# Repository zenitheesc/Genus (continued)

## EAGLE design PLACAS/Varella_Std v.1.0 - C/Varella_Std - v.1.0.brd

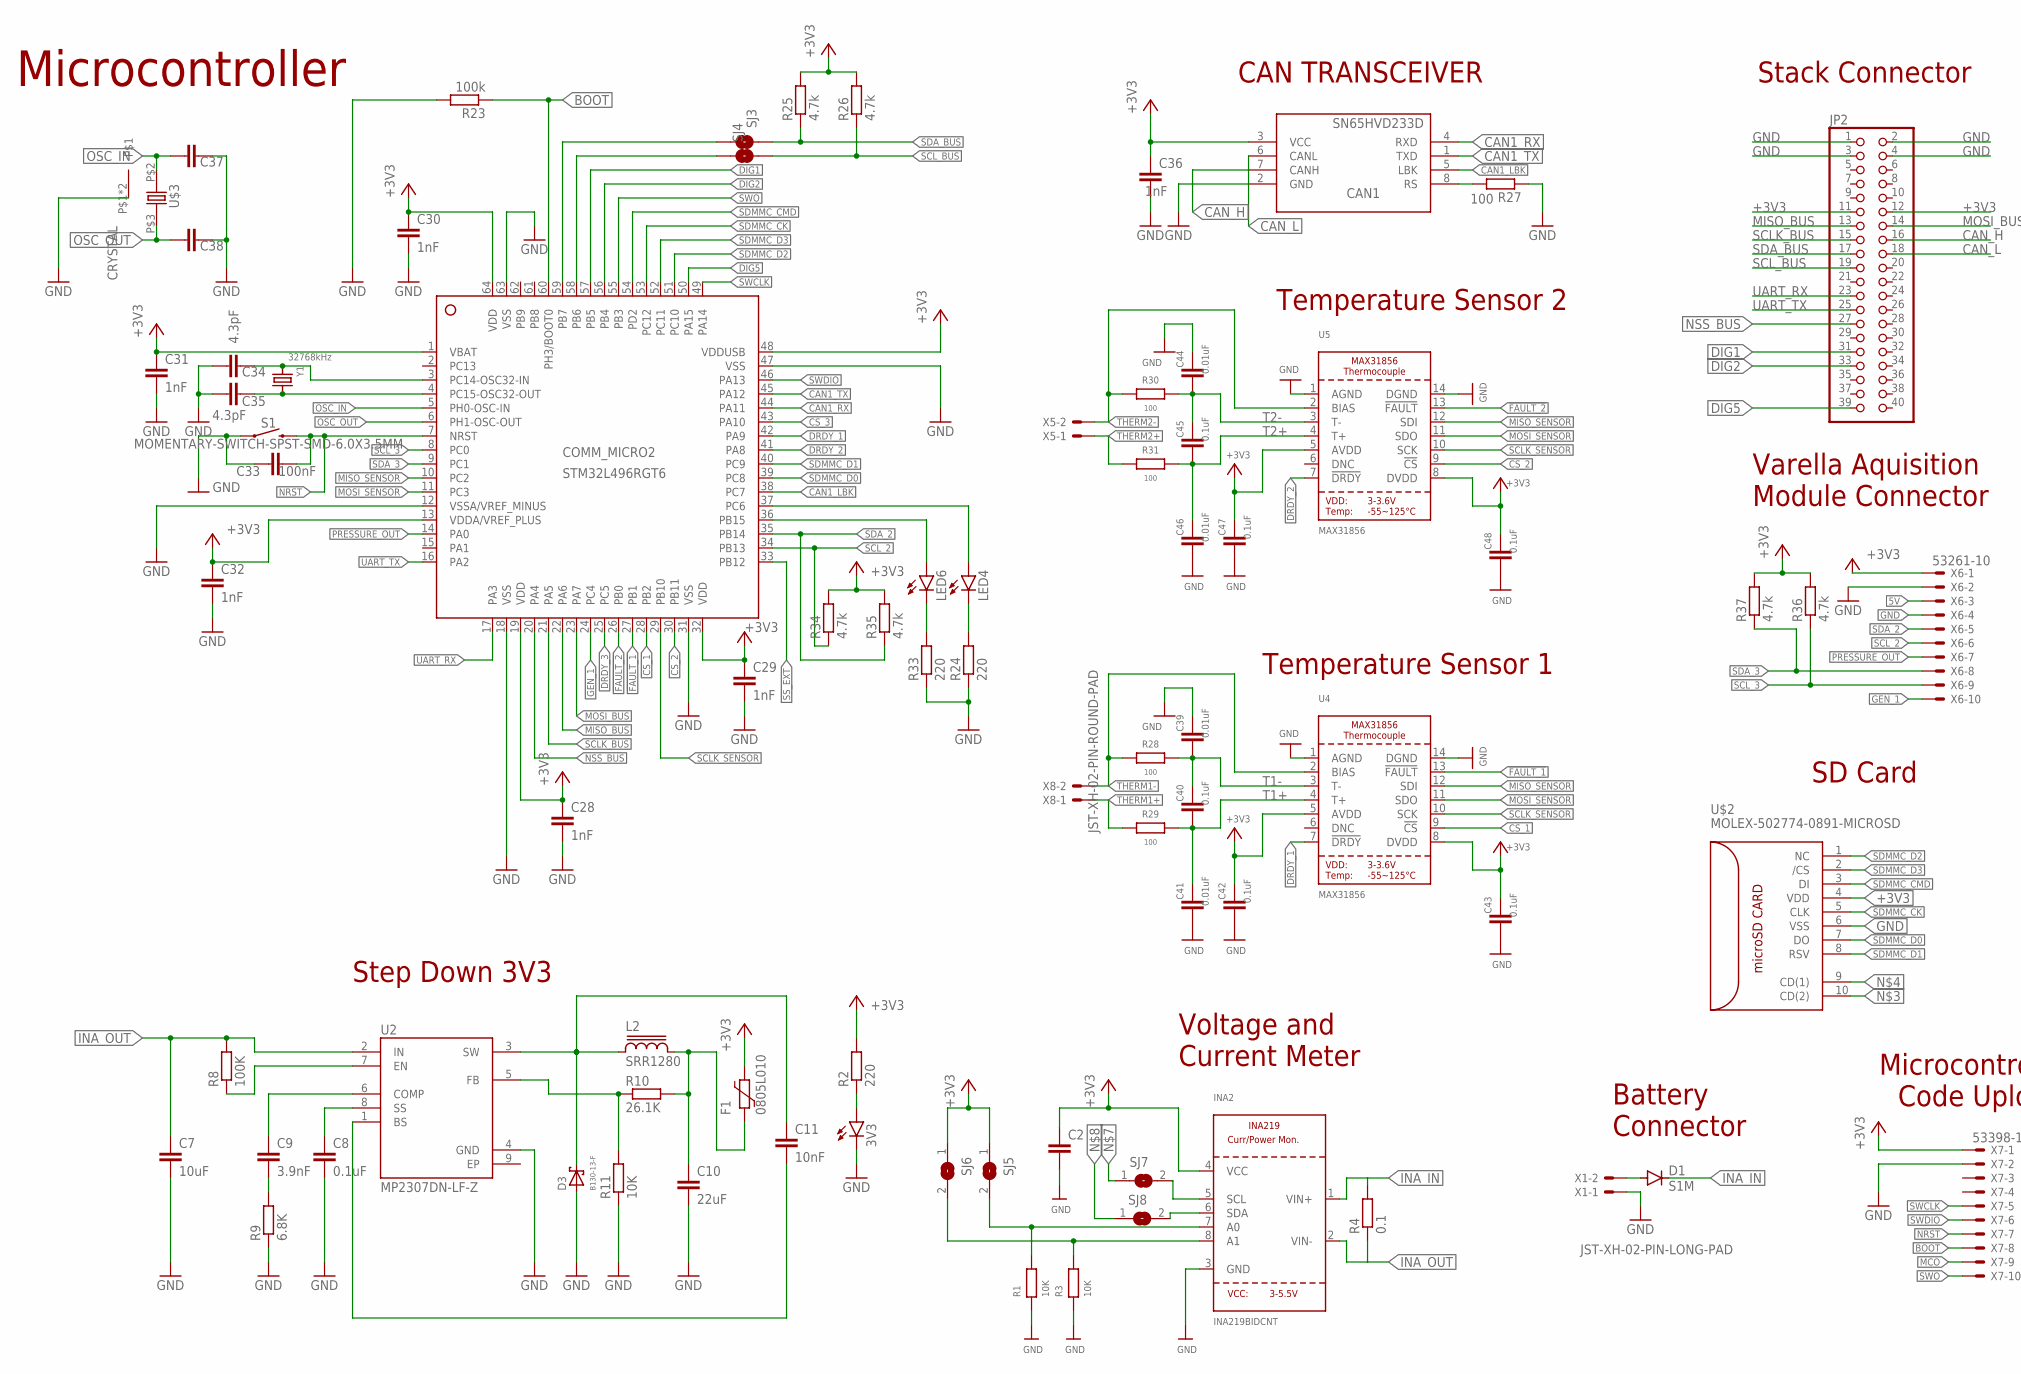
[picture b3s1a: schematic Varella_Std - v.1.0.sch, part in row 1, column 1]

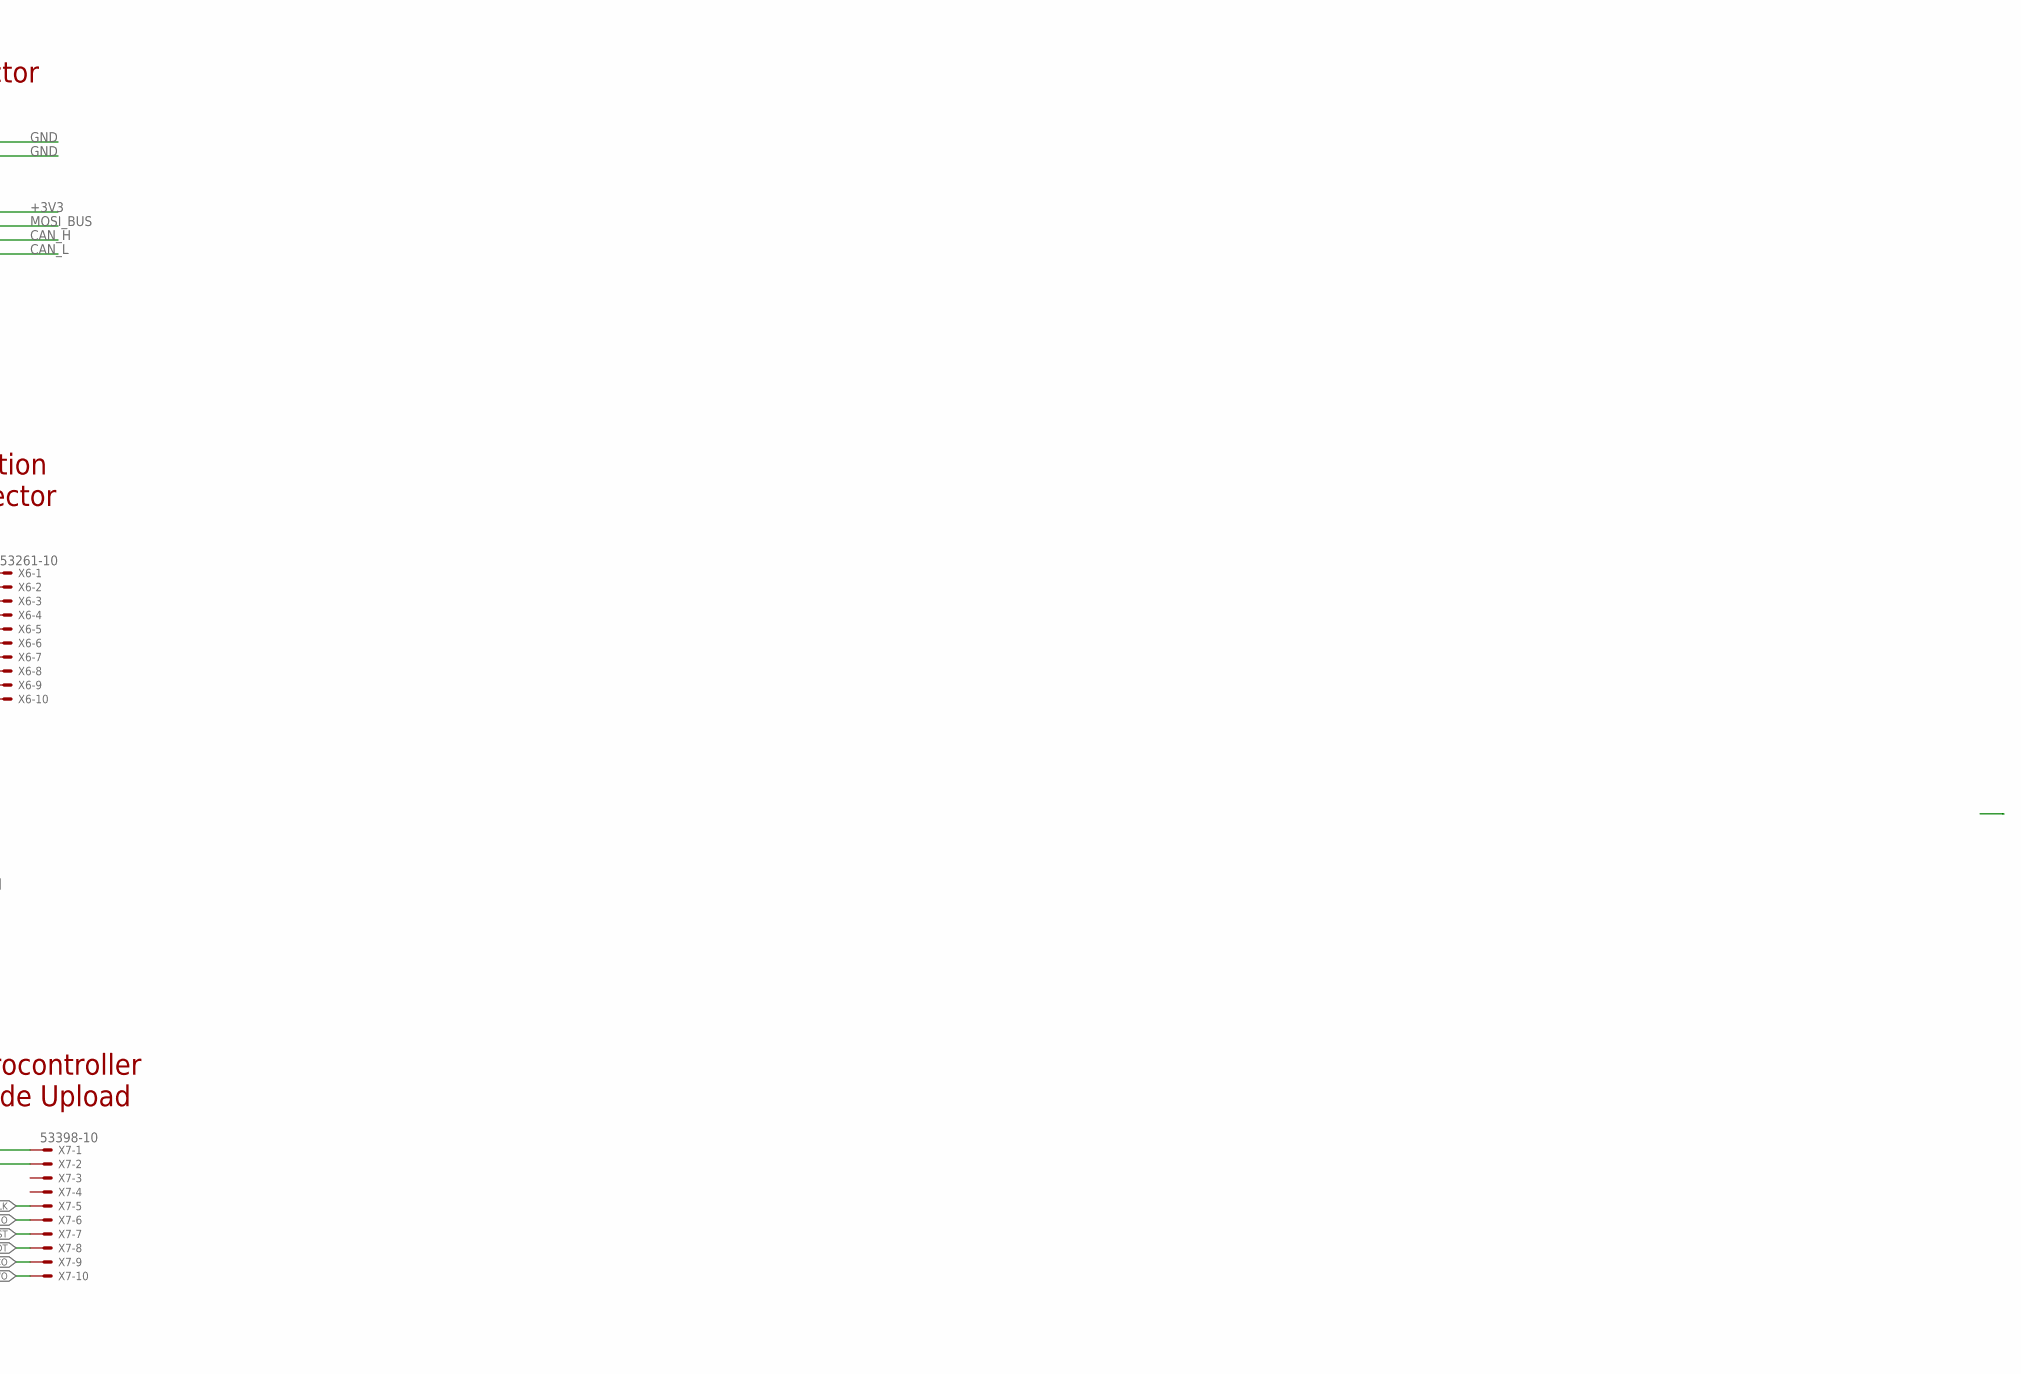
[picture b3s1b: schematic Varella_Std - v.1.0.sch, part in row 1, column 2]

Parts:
3V3: LEDCHIP-LED0805; CHIP-LED0805
C2, C37, C38: C-EUC0805; C0805
C7: 10uF; C0805
C8, C40, C42, C43, C45, C47, C48: 0.1uF; C0805
C9: 3.9nF; C0805
C10: 22uF; C0805
C11: 10nF; C0805
C28, C29, C30, C31, C32, C36: 1nF; C0805
C33: 100nF; C0805
C34, C35: 4.3pF; C0805
C39, C41, C44, C46: 0.01uF; C0805
CAN1: SN65HVD233D; SOIC8
COMM_MICRO2: STM32L496RGT6; LQFP64_10X10
D1: S1M; SMA
D3: B130-13-F; SMA
F1: 0805L010; 0805L
INA2: INA219BIDCNT; SOT23-8
JP2: PINHD-2X20; 2X20
L2: SRR1280
LED4, LED6: LEDCHIP-LED0805; CHIP-LED0805
R1, R3, R11: 10K; R0805
R2, R24, R33: 220; R0805
R4: 0.1; R2512
R8: 100K; R0805
R9: 6.8K; R0805
R10: 26.1K; R0805
R23: 100k; R0805
R25, R26, R34, R35, R36, R37: 4.7k; R0805
R27, R28, R29, R30, R31: 100; R0805
S1: MOMENTARY-SWITCH-SPST-SMD-6.0X3.5MM; TACTILE_SWITCH_SMD_6.0X3.5MM
SJ3, SJ4: SMD-JUMPER-2
SJ5, SJ6, SJ7, SJ8: SOLDERJUMPERREFLOW_NOPASTE; SOLDERJUMPER_REFLOW_NOPASTE
U2: MP2307DN-LF-Z; SOIC127P600X170-9N
U4, U5: MAX31856; TSSOP14
U$2: MOLEX-502774-0891-MICROSD
U$3: CRYSTAL; CRYSTAL_SMD
X1: JST-XH-02-PIN-LONG-PAD; JST-XH-02-PACKAGE-LONG-PAD
X5, X8: JST-XH-02-PIN-ROUND-PAD; JST-XH-02-PACKAGE-ROUND-PAD
X6: 53261-10
X7: 53398-10
Y1: 32768kHz; CRYSTAL_8X3.8

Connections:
5V: X6.3
!FAULT_1: COMM_MICRO2.27 (PB1), U4.13 (!FAULT)
!FAULT_2: COMM_MICRO2.26 (PB0), U5.13 (!FAULT)
+3V3: C2.1, C28.1, C29.1, C30.1, C31.1, C32.1, C36.1, C42.1, C43.1, C47.1, C48.1, CAN1.3 (VCC), COMM_MICRO2.1 (VBAT), COMM_MICRO2.13 (VDDA/VREF_PLUS), COMM_MICRO2.19 (VDD), COMM_MICRO2.32 (VDD), COMM_MICRO2.48 (VDDUSB), COMM_MICRO2.64 (VDD), F1.1, INA2.4 (VCC), JP2.11, JP2.12, R2.2, R25.2, R26.2, R34.2, R35.2, R36.2, R37.2, SJ5.1, SJ6.1, U4.5 (AVDD), U4.8 (DVDD), U5.5 (AVDD), U5.8 (DVDD), U$2.4 (VDD), X6.1, X7.1
BOOT: COMM_MICRO2.60 (PH3/BOOT0), R23.1, X7.8
CAN1_LBK: CAN1.5 (LBK), COMM_MICRO2.38 (PC7)
CAN1_RX: CAN1.4 (RXD), COMM_MICRO2.44 (PA11)
CAN1_TX: CAN1.1 (TXD), COMM_MICRO2.45 (PA12)
CAN_H: CAN1.7 (CANH), JP2.16
CAN_L: CAN1.6 (CANL), JP2.18
CS_1: COMM_MICRO2.28 (PB2), U4.9 (!CS)
CS_2: COMM_MICRO2.30 (PB11), U5.9 (!CS)
CS_3: COMM_MICRO2.43 (PA10)
DIG1: COMM_MICRO2.57 (PB5), JP2.31
DIG2: COMM_MICRO2.56 (PB4), JP2.33
DIG5: COMM_MICRO2.50 (PA15), JP2.39
DRDY_1: COMM_MICRO2.42 (PA9), U4.7 (!DRDY)
DRDY_2: COMM_MICRO2.41 (PA8), U5.7 (!DRDY)
DRDY_3: COMM_MICRO2.25 (PC5)
EP: U2.9 (EP)
GEN_1: COMM_MICRO2.24 (PC4), X6.10
GND: 3V3.C, C2.2, C7.2, C8.2, C10.2, C28.2, C29.2, C30.2, C31.2, C32.2, C33.1, C34.1, C35.1, C36.2, C37.2, C38.2, C39.1, C41.2, C42.2, C43.2, C44.1, C46.2, C47.2, C48.2, CAN1.2 (GND), COMM_MICRO2.12 (VSSA/VREF_MINUS), COMM_MICRO2.18 (VSS), COMM_MICRO2.31 (VSS), COMM_MICRO2.47 (VSS), COMM_MICRO2.63 (VSS), D3.A, INA2.3 (GND), JP2.1, JP2.2, JP2.3, JP2.4, R1.1, R3.1, R9.1, R11.1, R23.2, R24.1, R27.1, R33.1, S1.1, U2.4 (GND), U4.1 (AGND), U4.14 (DGND), U5.1 (AGND), U5.14 (DGND), U$2.6 (VSS), U$3.P$1, U$3.P$4, X1.1, X6.2, X6.4, X7.2
INA_IN: D1.C, INA2.1 (VIN+), R4.2
INA_OUT: C7.1, INA2.2 (VIN-), R4.1, R8.2, U2.2 (IN)
MCO: X7.9
MISO_BUS: COMM_MICRO2.22 (PA6), JP2.13
MISO_SENSOR: COMM_MICRO2.10 (PC2), U4.12 (SDI), U5.12 (SDI)
MOSI_BUS: COMM_MICRO2.23 (PA7), JP2.14
MOSI_SENSOR: COMM_MICRO2.11 (PC3), U4.11 (SDO), U5.11 (SDO)
unnamed: D1.A, X1.2
unnamed: 3V3.A, R2.1
unnamed: INA2.8 (A1), R3.2, SJ6.2, SJ7.1
unnamed: INA2.7 (A0), R1.2, SJ5.2, SJ8.1
unnamed: INA2.5 (SCL), SJ7.2
unnamed: INA2.6 (SDA), SJ8.2
unnamed: R8.1, U2.7 (EN)
unnamed: C9.2, R9.2
unnamed: C8.1, U2.8 (SS)
unnamed: C9.1, U2.6 (COMP)
unnamed: C11.1, D3.C, L2.1, U2.3 (SW)
unnamed: R10.1, R11.2, U2.5 (FB)
unnamed: C11.2, U2.1 (BS)
unnamed: COMM_MICRO2.37 (PC6), LED4.A
unnamed: LED4.C, R24.2
unnamed: C34.2, COMM_MICRO2.3 (PC14-OSC32-IN), Y1.P$1 (1)
unnamed: C35.2, COMM_MICRO2.4 (PC15-OSC32-OUT), Y1.P$4 (2)
unnamed: COMM_MICRO2.59 (PB7), SJ3.1
unnamed: COMM_MICRO2.58 (PB6), SJ4.1
unnamed: CAN1.8 (RS), R27.2
unnamed: COMM_MICRO2.36 (PB15), LED6.A
unnamed: LED6.C, R33.2
NRST: C33.2, COMM_MICRO2.7 (NRST), S1.2, X7.7
NSS_BUS: COMM_MICRO2.20 (PA4), JP2.27
OSC_IN: C37.1, COMM_MICRO2.5 (PH0-OSC-IN), U$3.P$2 (1)
OSC_OUT: C38.1, COMM_MICRO2.6 (PH1-OSC-OUT), U$3.P$3 (2)
OUT: C10.1, F1.2, L2.2, R10.2
PRESSURE_OUT: COMM_MICRO2.14 (PA0), X6.7
SCLK_BUS: COMM_MICRO2.21 (PA5), JP2.15
SCLK_SENSOR: COMM_MICRO2.29 (PB10), U4.10 (SCK), U5.10 (SCK)
SCL_2: COMM_MICRO2.34 (PB13), R34.1, X6.6
SCL_3: COMM_MICRO2.8 (PC0), R36.1, X6.9
SCL_BUS: JP2.19, R26.1, SJ4.2
SDA_2: COMM_MICRO2.35 (PB14), R35.1, X6.5
SDA_3: COMM_MICRO2.9 (PC1), R37.1, X6.8
SDA_BUS: JP2.17, R25.1, SJ3.2
SDMMC_CK: COMM_MICRO2.53 (PC12), U$2.5 (CLK)
SDMMC_CMD: COMM_MICRO2.54 (PD2), U$2.3 (DI)
SDMMC_D0: COMM_MICRO2.39 (PC8), U$2.7 (DO)
SDMMC_D1: COMM_MICRO2.40 (PC9), U$2.8 (RSV)
SDMMC_D2: COMM_MICRO2.51 (PC10), U$2.1 (NC)
SDMMC_D3: COMM_MICRO2.52 (PC11), U$2.2 (/CS)
SS_EXT: COMM_MICRO2.33 (PB12)
SWCLK: COMM_MICRO2.49 (PA14), X7.5
SWDIO: COMM_MICRO2.46 (PA13), X7.6
SWO: COMM_MICRO2.55 (PB3), X7.10
T1+: C40.2, C41.1, R29.2, U4.4 (T+)
T1-: C39.2, C40.1, R28.2, U4.3 (T-)
T2+: C45.2, C46.1, R31.2, U5.4 (T+)
T2-: C44.2, C45.1, R30.2, U5.3 (T-)
THERM1+: R29.1, X8.1
THERM1-: R28.1, U4.2 (BIAS), X8.2
THERM2+: R31.1, X5.1
THERM2-: R30.1, U5.2 (BIAS), X5.2
UART_RX: COMM_MICRO2.17 (PA3), JP2.23
UART_TX: COMM_MICRO2.16 (PA2), JP2.25

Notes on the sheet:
Battery Connector
Voltage and Current Meter
Step Down 3V3
Microcontroller Code Upload
Microcontroller
CAN TRANSCEIVER
Varella Aquisition Module Connector
Temperature Sensor 1
Temperature Sensor 2
Stack Connector
SD Card

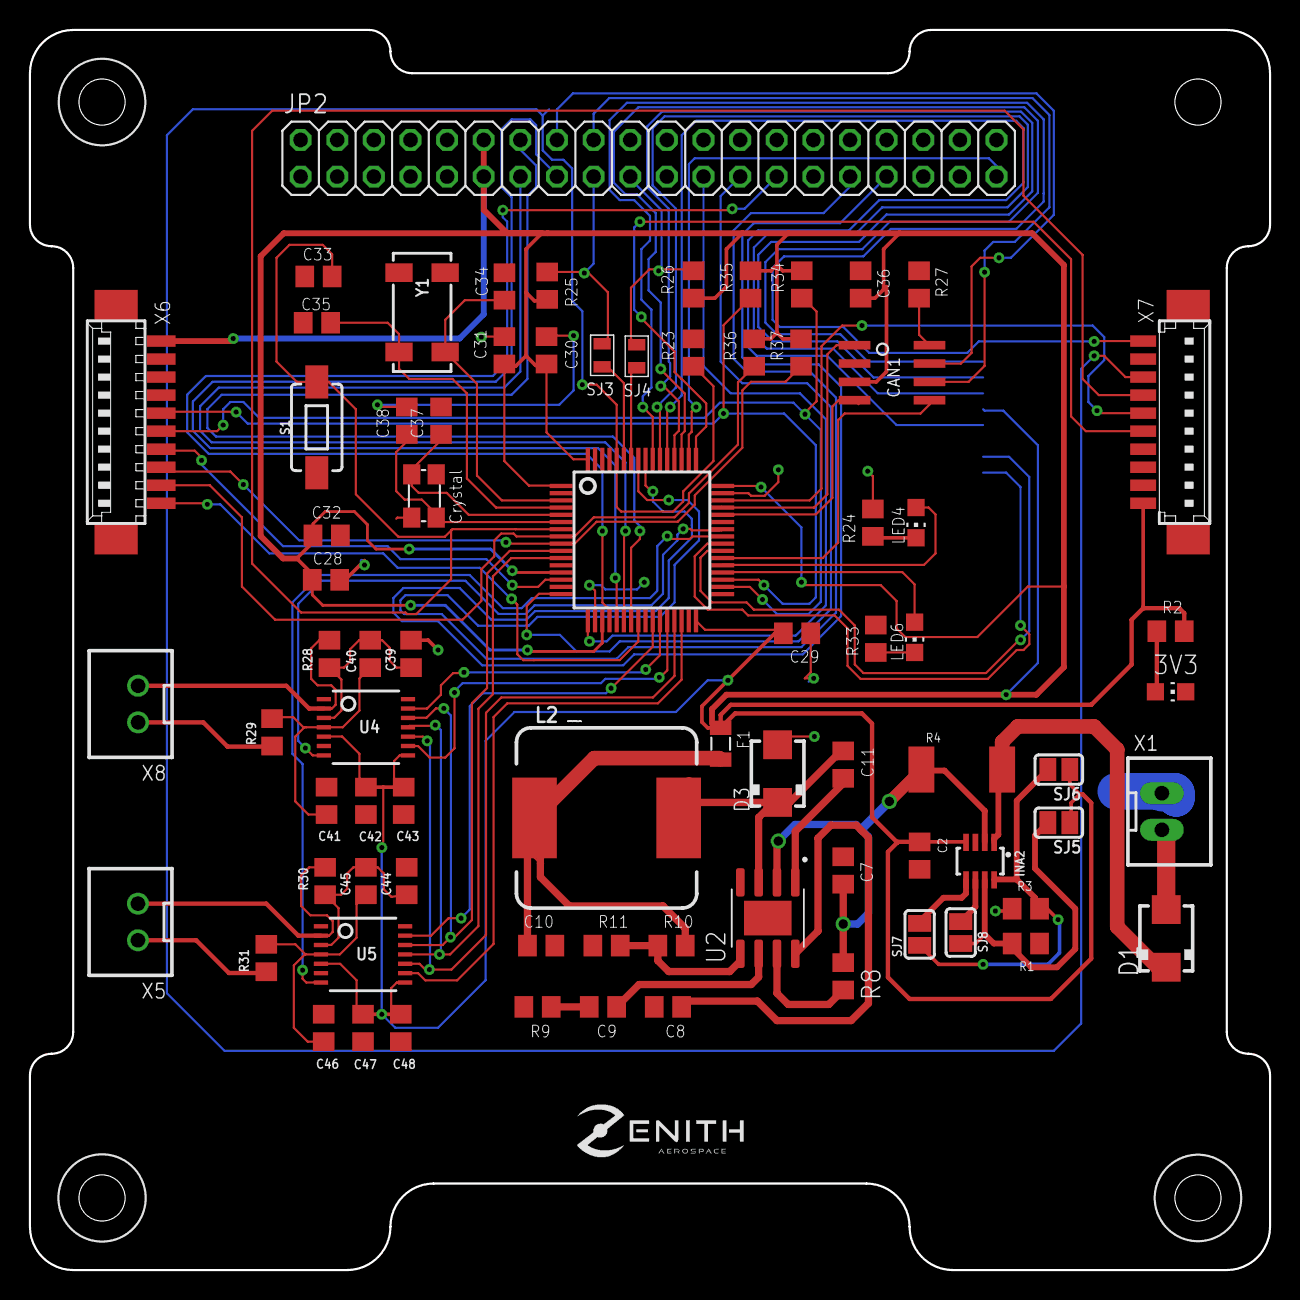
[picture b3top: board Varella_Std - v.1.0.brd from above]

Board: 2 copper layers, 86.0 x 86.0 mm, 78 parts (1 on the bottom side), 79 nets.
